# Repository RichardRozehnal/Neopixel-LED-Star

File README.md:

# Neopixel LED Star

Hvězda se 44 neopixel LEDkami zobrazuje 21 efektů. Efekty se automaticky přepínají po 2 minutách, ale je možné je přepínat i ručně tlačítkem. Tlačitkem lze také volit barvu LEDek a jejich jas.

#### Funkce tlačítka:
1 stisk přepíná efekty (celkem 21 efektů + jedna pozice pro automatické přepínání)  
2 rychlé stisky mění barvu (pouze při efektu, který používá jednu barvu)  
1 dlouhý stisk mění jas LEDek (celkem 5 nastavení jasu)  

## Seznam součástek

|    Ref   | Qnty |          Value         |     Cmp name     |
|:--------:|:----:|:----------------------:|:----------------:|
| C1,      | 1    | 1000uF/10V             | C_Polarized      |
| C2, C3,  | 2    | 10uF                   | C                |
| C4, C6,  | 2    | 100nF                  | C                |
| C5,      | 1    | 4u7                    | C                |
| J1,      | 1    | Power Supply Jack      | Conn_01x02       |
| J2,      | 1    | Neopixel solder points | Conn_01x03       |
| J3,      | 1    | Programming Connector  | Conn_01x04       |
| R1,      | 1    | 470R                   | R                |
| SW1,     | 1    | Switch                 | SW_Push          |
| U1,      | 1    | HT7533                 | HT75xx-1-SOT89   |
| U2,      | 1    | STM32G031J6M6          | STM32G031J6M6    |
| U3,      | 1    | 74AHCT1G125QW5-7       | 74AHCT1G125QW5-7 |

## Další fotky

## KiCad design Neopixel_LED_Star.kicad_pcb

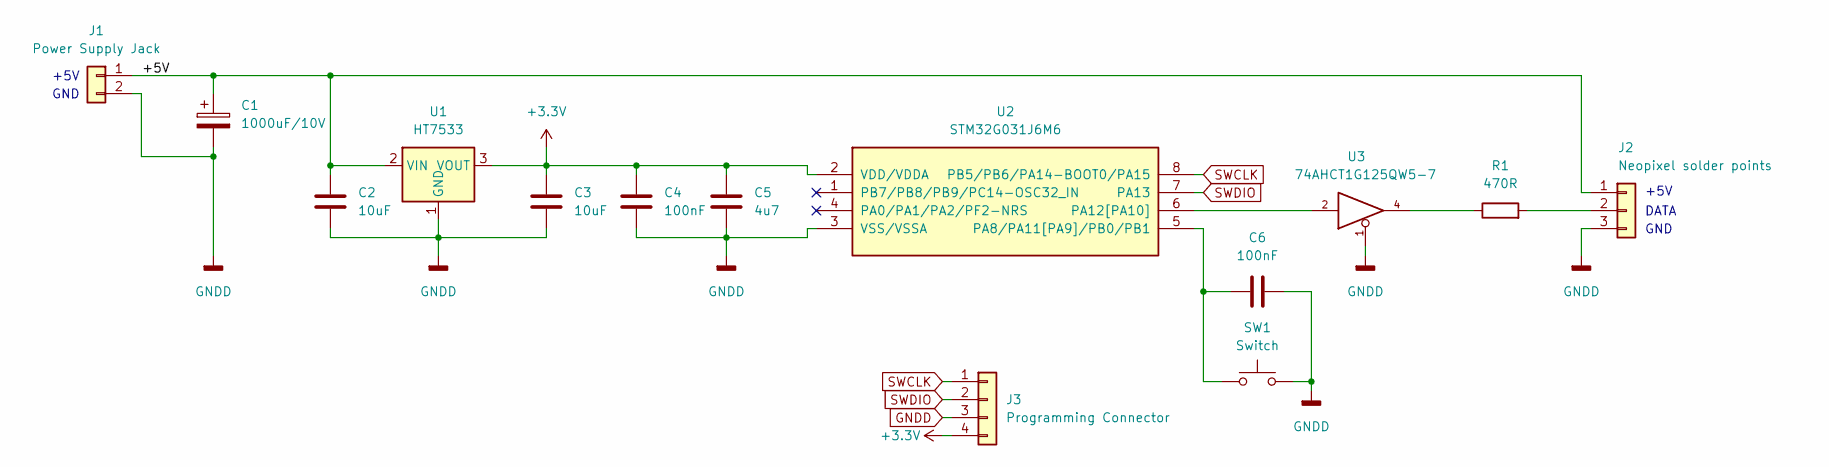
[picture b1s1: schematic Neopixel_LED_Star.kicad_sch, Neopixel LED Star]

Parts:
C1: 1000uF/10V; CP_Radial_D10.0mm_P5.00mm
C2, C3: 10uF; C_1206_3216Metric
C4, C6: 100nF; C_1206_3216Metric
C5: 4u7; C_1206_3216Metric
J1: Power Supply Jack; BarrelJack_Horizontal_3.5x1.3
J2: Neopixel solder points; PinHeader_1x03_P2.54mm_Vertical
J3: Programming Connector; PinHeader_1x04_P2.54mm_Vertical
R1: 470R; R_1206_3216Metric
SW1: Switch; SW_PUSH_6mm_H4.3mm
U1: HT7533; SOT-89-3
U2: STM32G031J6M6; SOIC-8_3.9x4.9mm_P1.27mm
U3: 74AHCT1G125QW5-7; SOT-23-5

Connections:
+3V3: C3.1, C4.1, C5.1, J3.4, U1.3 (VOUT), U2.2 (VDD/VDDA)
+5V: C1.1, C2.1, J1.1, J2.1, U1.2 (VIN), U3.5 (+5V)
GNDD: C1.2, C2.2, C3.2, C4.2, C5.2, C6.2, J1.2, J2.3, J3.3, SW1.2, U1.1 (GND), U2.3 (VSS/VSSA), U3.1, U3.3 (GNDD)
unnamed: C6.1, SW1.1, U2.5 (PA8/PA11[PA9]/PB0/PB1)
unnamed: J2.2, R1.2
unnamed: R1.1, U3.4
unnamed: U2.6 (PA12[PA10]), U3.2
SWCLK: J3.1, U2.8 (PB5/PB6/PA14-BOOT0/PA15)
SWDIO: J3.2, U2.7 (PA13)

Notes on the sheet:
+5V
DATA
GND

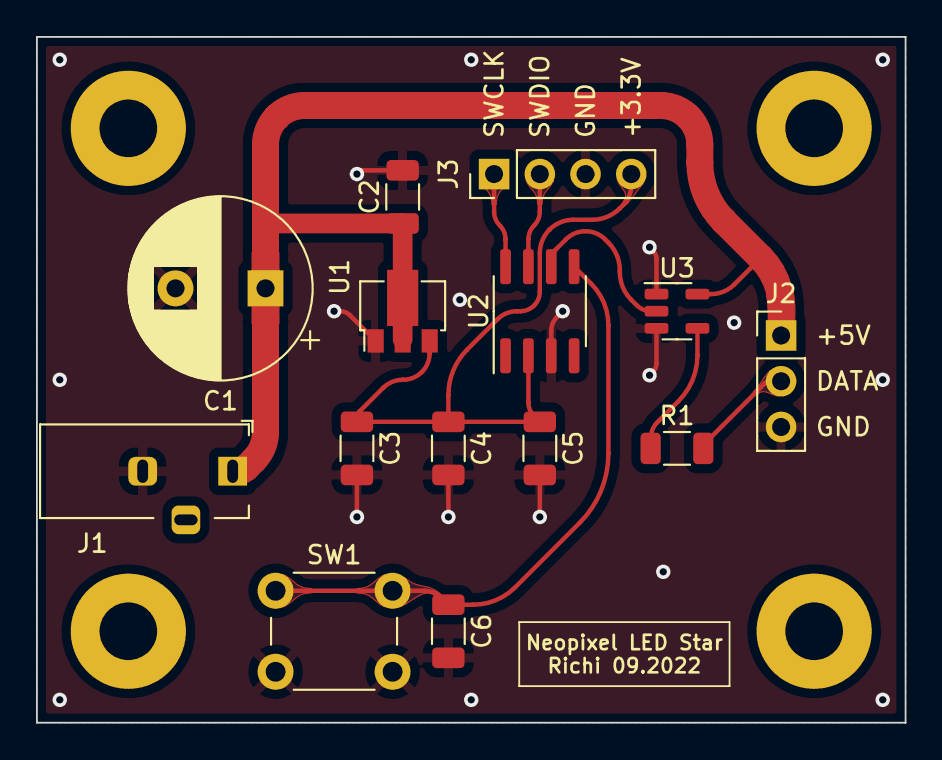
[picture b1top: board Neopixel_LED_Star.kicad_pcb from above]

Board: 2 copper layers, 48.3 x 38.1 mm, 14 parts (0 on the bottom side), 9 nets.

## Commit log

2022-12-23 Create . ...
